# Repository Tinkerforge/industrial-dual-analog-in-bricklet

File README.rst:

Industrial Dual Analog In Bricklet
==================================

This repository contains the firmware source code and the hardware design
files. The documentation generator configs can be found at
https://github.com/Tinkerforge/generators

Repository Content
------------------

software/:
 * examples/: Examples for all supported languages
 * build/: Compiled files
 * src/: Source code of firmware
 * Makefile: Makefile to build project

hardware/:
 * Contains KiCad project files and additionally schematics as PDF

datasheets/:
 * Contains datasheets for sensors and complex ICs that are used

Hardware
--------

The hardware is designed with the open source EDA Suite KiCad
(http://www.kicad.org). Before you are able to open the files,
you have to install the Tinkerforge kicad-libraries
(https://github.com/Tinkerforge/kicad-libraries). You can either clone
them directly in hardware/ or clone them in a separate folder and
symlink them into hardware/
(ln -s kicad_path/kicad-libraries project_path/hardware). After that you
can open the .pro file in hardware/ with KiCad and from there view and
modify the schematics and the PCB layout.

Software
--------

If you want to do your own Brick/Bricklet firmware development we highly
recommend that you use our build environment setup script and read the
tutorial (https://www.tinkerforge.com/en/doc/Tutorials/Tutorial_Build_Environment/Tutorial.html).

To compile the C code we recommend you to install the newest GNU Arm Embedded
Toolchain (https://launchpad.net/gcc-arm-embedded/+download).
You also need to install bricklib (https://github.com/Tinkerforge/bricklib)
and brickletlib (https://github.com/Tinkerforge/brickletlib).

You can either clone it directly in software/src/ or clone it in a
separate folder and symlink it into software/src/
(ln -s bricklib_path/bricklib project_path/software/src/ and
ln -s brickletlib_path/brickletlib project_path/software/src/).
Finally make sure to have CMake installed
(http://www.cmake.org/cmake/resources/software.html).

After that you can build the firmware by invoking make in software/.
The firmware (.bin) can then be found in software/build/ and uploaded
with brickv (click button "Flashing" on start screen).

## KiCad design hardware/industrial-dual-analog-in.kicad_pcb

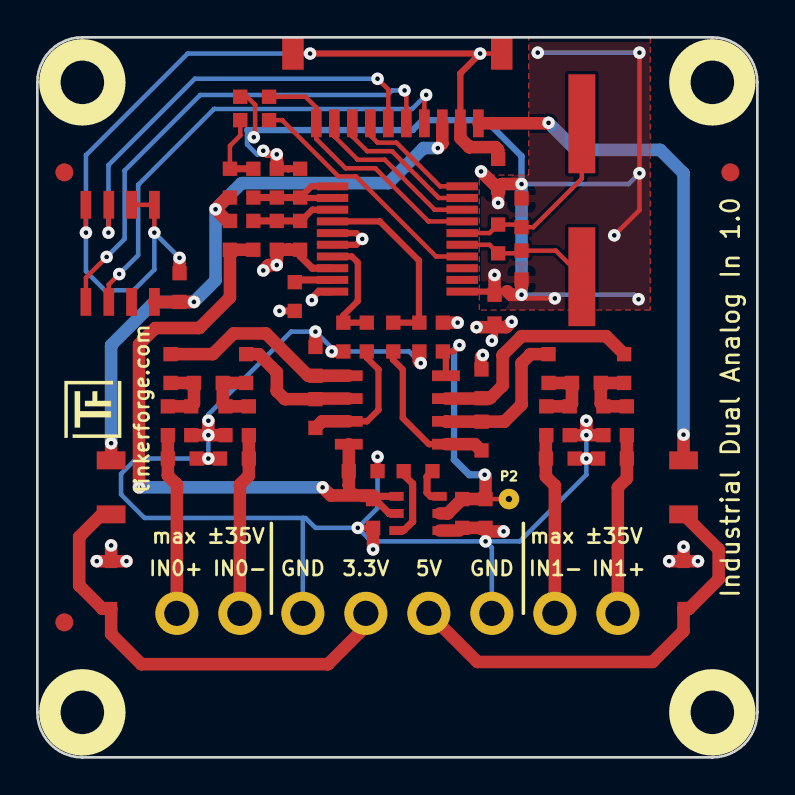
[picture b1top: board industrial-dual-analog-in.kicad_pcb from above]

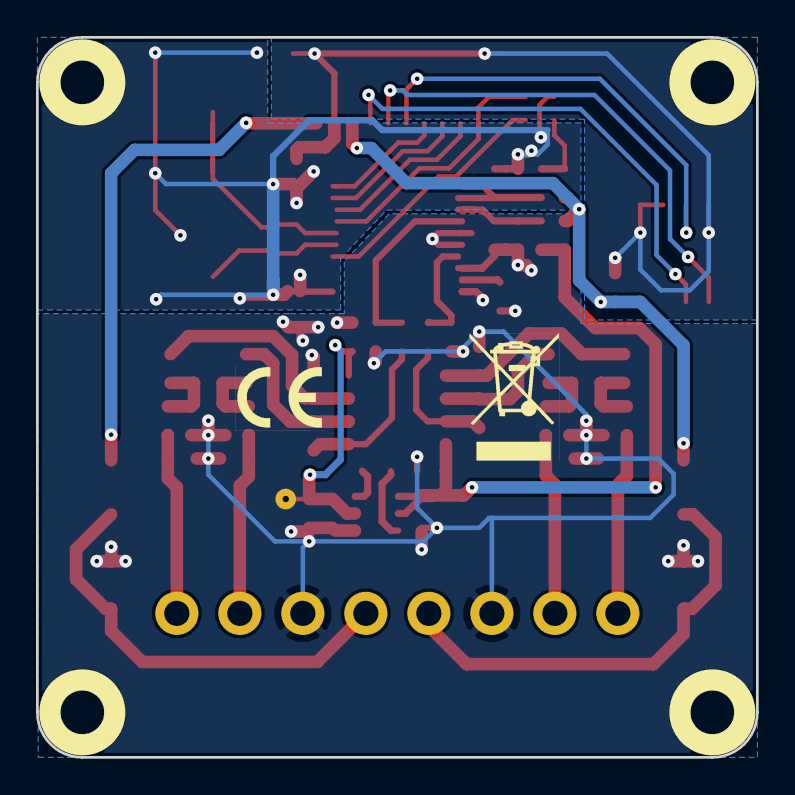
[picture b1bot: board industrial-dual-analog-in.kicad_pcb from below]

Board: 2 copper layers, 40.0 x 40.0 mm, 70 parts (2 on the bottom side), 41 nets.

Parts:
C1, C2, C6, C7, C12, C14, C15: 100nF; C0603
C3, C4, C5: 3.3µF; C0603
C8, C9: 18pF; C0603
C10, C11: 1nF; C0603
C13, C16: 10µF; C0603
C17, C19, C20, C22: 15pF; C0603
C18, C21: 150pF; C0603
D1: CDSOD323-T05SC; SOD-323
D2: CDSOD323-T03SC; SOD-323
F1, F2: OZCJ0035FF2G; F1206
FB1, FB2, FB3: FILTER; C0603
Fiducial_Mark: VAL**; Fiducial_Mark
Fiducial_Mark#2, Fiducial_Mark#3: VAL**; Fiducial_Mark
P1: CON-SENSOR
P2: CONN_1; PINTST
P3: CONN_8; OQ_8P
R1: 0; R0603
R2: 1M; R0603
R3, R21, R22, R23, R24: 100k; R0603
R4: DNP; R0603
R5, R6: 68.1; R0603
R7, R12, R17, R18, R19, R20: 10; R0603
R8, R9, R10, R11: 4k7/10ppm; R0603
R13, R14, R15, R16: 280k/10ppm; R0603
U1: LMV342IDRG4; SOIC8
U2: LM2664; SOT23-6
U3: M24C64; SOIC8
U4: MCP3911; SSOP20-53
U5, U6, U7, U8: DRILL; DRILL_NP
VAL: CE_5mm
VAL#2: WEEE_7mm
X1: 10MHz; HC49_US

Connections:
3V3: C7.1, F2.1, FB1.1, FB2.1, P1.3, U3.8
+3.3VADC: C1.2, C3.1, FB1.2, R12.1, U1.8, U2.4, U2.5
+3.3VP: FB2.2, R3.1, R7.1
+5V: F1.1, P1.1
-VAA: C2.1, C4.1, C6.2, P2.1, U1.4, U2.2
ADC0: C10.2, R5.1, U4.7
ADC1: C11.2, R6.1, U4.4
AGND: C1.1, C2.2, C3.2, C4.2, C6.1, C10.1, C11.1, C14.1, C15.1, C16.1, C17.2, C19.1, C20.2, C22.1, D1.1, D2.1, P3.3, P3.6, R1.2, R10.1, R11.1, R21.2, R22.1, R23.2, R24.1, U2.1, U4.5, U4.6, U4.8, U4.10
DGND: C8.1, C9.1, C12.1, C13.1, FB3.2, R1.1, R4.2, U4.11
GND: C7.2, FB3.1, P1.2, P1.EP, U3.1, U3.2, U3.4
unnamed: C5.1, U2.6
unnamed: C5.2, U2.3
unnamed: C8.2, R2.1, U4.16, X1.1
unnamed: C9.2, R2.2, U4.15, X1.2
unnamed: C12.2, C13.2, R7.2, U4.1, U4.2
unnamed: C14.2, U4.9
unnamed: C15.2, C16.2, R12.2, U4.3
unnamed: C17.1, C18.2, R13.2, R17.1
unnamed: C18.1, C19.2, R14.2, R18.1
unnamed: C20.1, C21.2, R15.2, R19.1
unnamed: C21.1, C22.2, R16.2, R20.1
unnamed: D1.2, F1.2, P3.5
unnamed: D2.2, F2.2, P3.4
unnamed: P1.4, U3.6
unnamed: P1.5, U3.5
unnamed: P1.6, U3.3
unnamed: P1.7, U4.20
unnamed: P1.8, U4.19
unnamed: P1.9, U4.18
unnamed: P1.10, R4.1, U4.17
unnamed: P3.1, R18.2, R22.2
unnamed: P3.2, R17.2, R21.1
unnamed: P3.7, R19.2, R23.1
unnamed: P3.8, R20.2, R24.2
unnamed: R3.2, U4.14
unnamed: R5.2, R8.1, U1.7
unnamed: R6.2, R9.1, U1.1
unnamed: R10.2, R14.1, U1.5
unnamed: R11.2, R16.1, U1.3
unnamed: R8.2, R13.1, U1.6
unnamed: R9.2, R15.1, U1.2

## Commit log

2015-01-16 Add WIP hint
2015-01-23 Add registers and control functions
2015-02-26 Add api for calibration and averaging
2015-02-26 Save calibration to EEPROM
2015-02-27 Get status every tick
    otherwise we can't handle the full 976 samples/sec
2015-03-02 windows: Stop cmake from searching for mingw32-make.exe
    Using MinGW Makefiles as generator makes cmake search for mingw32-make.exe
    which might not be installed because GnuWin32's make.exe is used instead.
2015-03-26 add hardware files
2015-03-26 add schematic
2015-03-27 add schematic update resistor values
2015-03-27 move description text
2015-03-31 Change divisor to production version divisor
    and swap channels to be correct in API
2015-04-02 add some protection circuits
2015-04-02 remove comment in schematic
2015-04-02 change jack description, order version
2015-04-16 change fuses
2015-04-20 Use correct channels for calibration
2015-04-24 capacitors defined, drc executed
2015-04-30 Add Python examples
2015-05-05 last_value is set in simple_bricklet code
2015-05-05 Add C examples
2015-05-05 Add C# examples
2015-05-05 Add Delphi examples
2015-05-05 Add Java examples
2015-05-05 Add JavaScript examples
2015-05-05 Add Perl examples
2015-05-05 Add PHP examples
2015-05-05 Add Ruby examples
2015-05-05 Add Shell examples
2015-05-05 Add VB.NET examples
2015-05-05 Add Matlab/Octave examples
2015-06-17 Resistor value changed from 280k to 277k
2015-06-19 Add LabVIEW and Mathematica examples
    Also clean up other examples.
2015-06-24 javascript: Clean up output creation
2015-06-25 octave: Handle short difference between Octave 3.6 and 3.8
    In Octave 3.6 a short is not automatically handled as a number.
2015-07-08 Function name fix in MATLAB example
2015-07-08 Add newline in MATLAB example
2015-07-23 Make JavaScript browser example textarea readonly
2015-07-27 Cleanup C/C++, C# and Java examples
2015-07-29 Reformat changelog
2015-07-31 Cleanup C/C++, C#, Java, Python and Ruby examples more
2015-08-03 update schematic
2015-08-04 change voltage calculation formula
2015-08-04 Whitespace
2015-08-07 Use full device class name in Python examples
2015-08-12 Fix minor warnings in C/C++ examples
2015-08-17 Cleanup Delphi examples
2015-08-18 Cleanup VB.NET examples
2015-08-19 Cleanup Perl examples
2015-09-09 Duplicate cmake call to fix bug during cmake creation
2015-10-16 Generator based example cleanup
2015-11-12 matlab: Fix callback handling for R2014a
    http://undocumentedmatlab.com/blog/matlab-callbacks-for-java-events-in-r2014a
2015-11-25 Include date and commit into changelog
2015-11-30 update filter value
2015-11-30 vbnet: Shorten long line
2016-01-22 Rename de/select to mcp3911_de/select
    Otherwise we get a conflict with system
    select(int __n, fd_set *__readfds, fd_set *__writefds)
    in newer GCC versions
2016-05-18 c: Add missing device destroy call
2016-07-01 Make the change UID comment more explicit
2017-04-13 csharp: Adapt example
2017-04-21 shell: Adapt example
2017-05-08 fix tvs diode orientation
2017-06-02 octave: Use javaObject instead of deprecated java_new
2017-06-02 Add comments
2017-07-28 Fix symbols (moved external symbols to tinkerforgelib)
2017-07-31 Enable Fab Layers, update footprints
2017-07-31 Add 3d information (final)
2017-07-31 Add 3d model (*.step & *.FCStd)
2017-08-16 fix description
2017-11-30 Update examples from generator
2017-12-07 mathematica: Also generate .nb files
2018-01-26 c: Fine-tune printf format
2018-02-02 Update examples
2018-02-19 javascript: Close div tag correctly
2018-02-20 Cleanup KiCad libraries config
    Ensure LibDir=kicad-libraries and LibName1=tinkerforge.
    Remove special library.
2018-05-11 Rename files
2018-05-24 perl: Use strict in examples
2018-07-11 Add Makefile with docker support
2018-07-11 Remove obsolete generate_makefile scripts
2018-07-11 Update directory structure and build instructions
2018-09-14 vbnet: Fix typo in comment
2018-11-06 Add rust examples
2018-11-07 rust: Accept host names for ip connection, fix naming inconsistencies
2018-11-07 rust: Rename callback receivers.
2018-12-14 Add go examples.
2018-12-14 go: Fix printf parameters.
2018-12-18 go: Change import path.
2018-12-18 go: Change import path again.
2018-12-20 rust: Reformat examples.
2019-01-24 mqtt: Add examples.
2019-01-24 mqtt: Fix example header.
2019-01-24 mqtt: Remove executable bit in example permissions.
2019-01-24 go: Minor example fixes.
2019-01-24 mqtt: Minor example fixes.
2019-03-25 mqtt: Fix example whitespace.
2019-03-28 mqtt: Fix whitespace.
2019-08-22 c: Adapt to bindings changes
2020-01-13 examples: Use python3 input instead of python2 raw_input.
2020-01-13 examples: mqtt: Remove trailing whitespace.
2020-04-14 mqtt: Fix device name format
2021-10-25 Update KiCad link
    https://www.kicad.org/blog/2021/10/Avoid-links-to-former-kicad-domain/
2022-07-06 Add license files.

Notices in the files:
hardware/industrial-dual-analog-in.kicad_pcb:
Copyright (©) 2015, B.Nordmeyer
Copyright Tinkerforge GmbH 2015.
This documentation describes Open Hardware and is licensed under the
CERN OHL v. 1.1.
